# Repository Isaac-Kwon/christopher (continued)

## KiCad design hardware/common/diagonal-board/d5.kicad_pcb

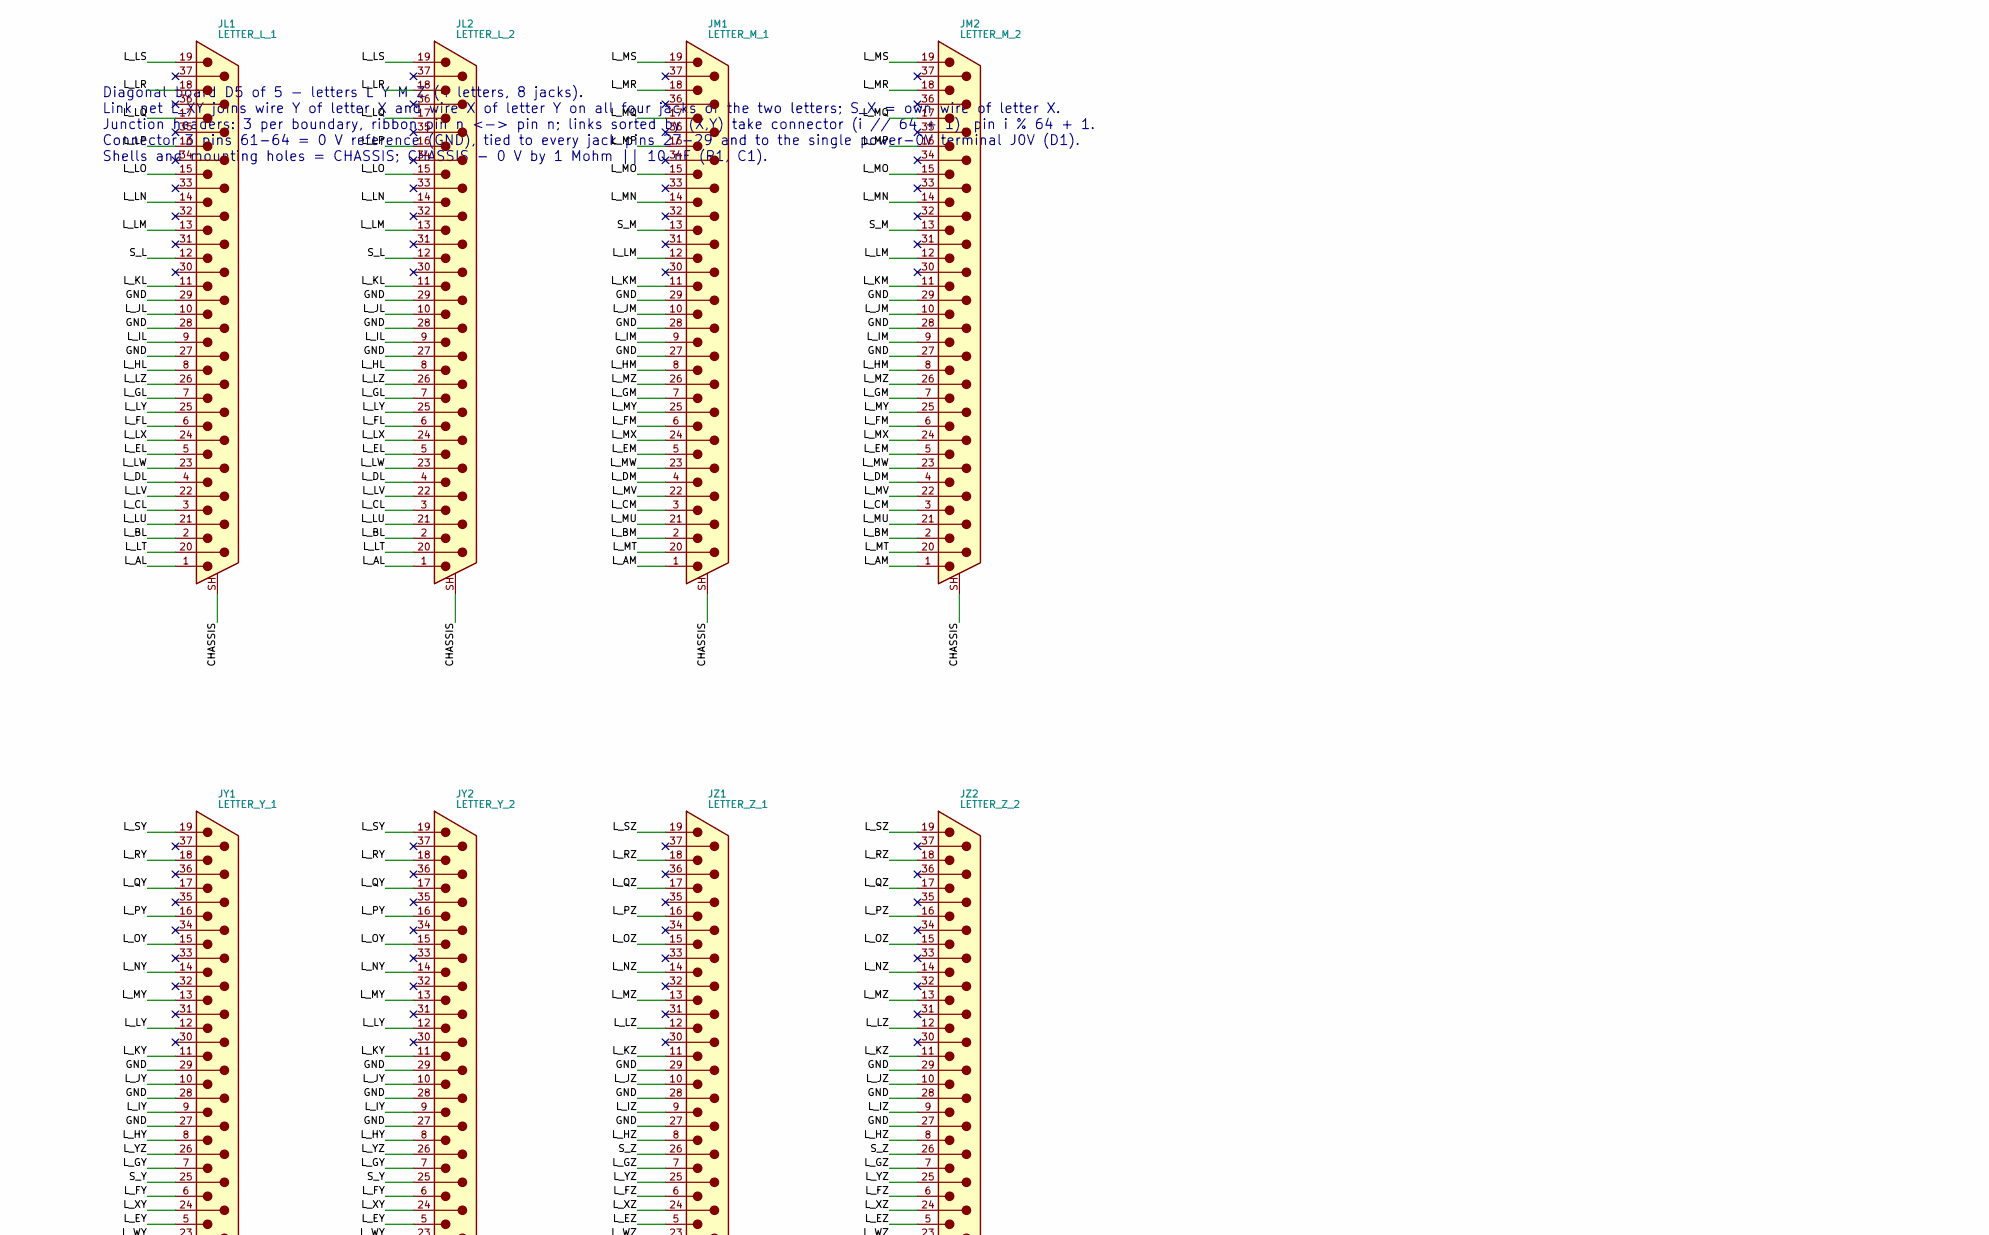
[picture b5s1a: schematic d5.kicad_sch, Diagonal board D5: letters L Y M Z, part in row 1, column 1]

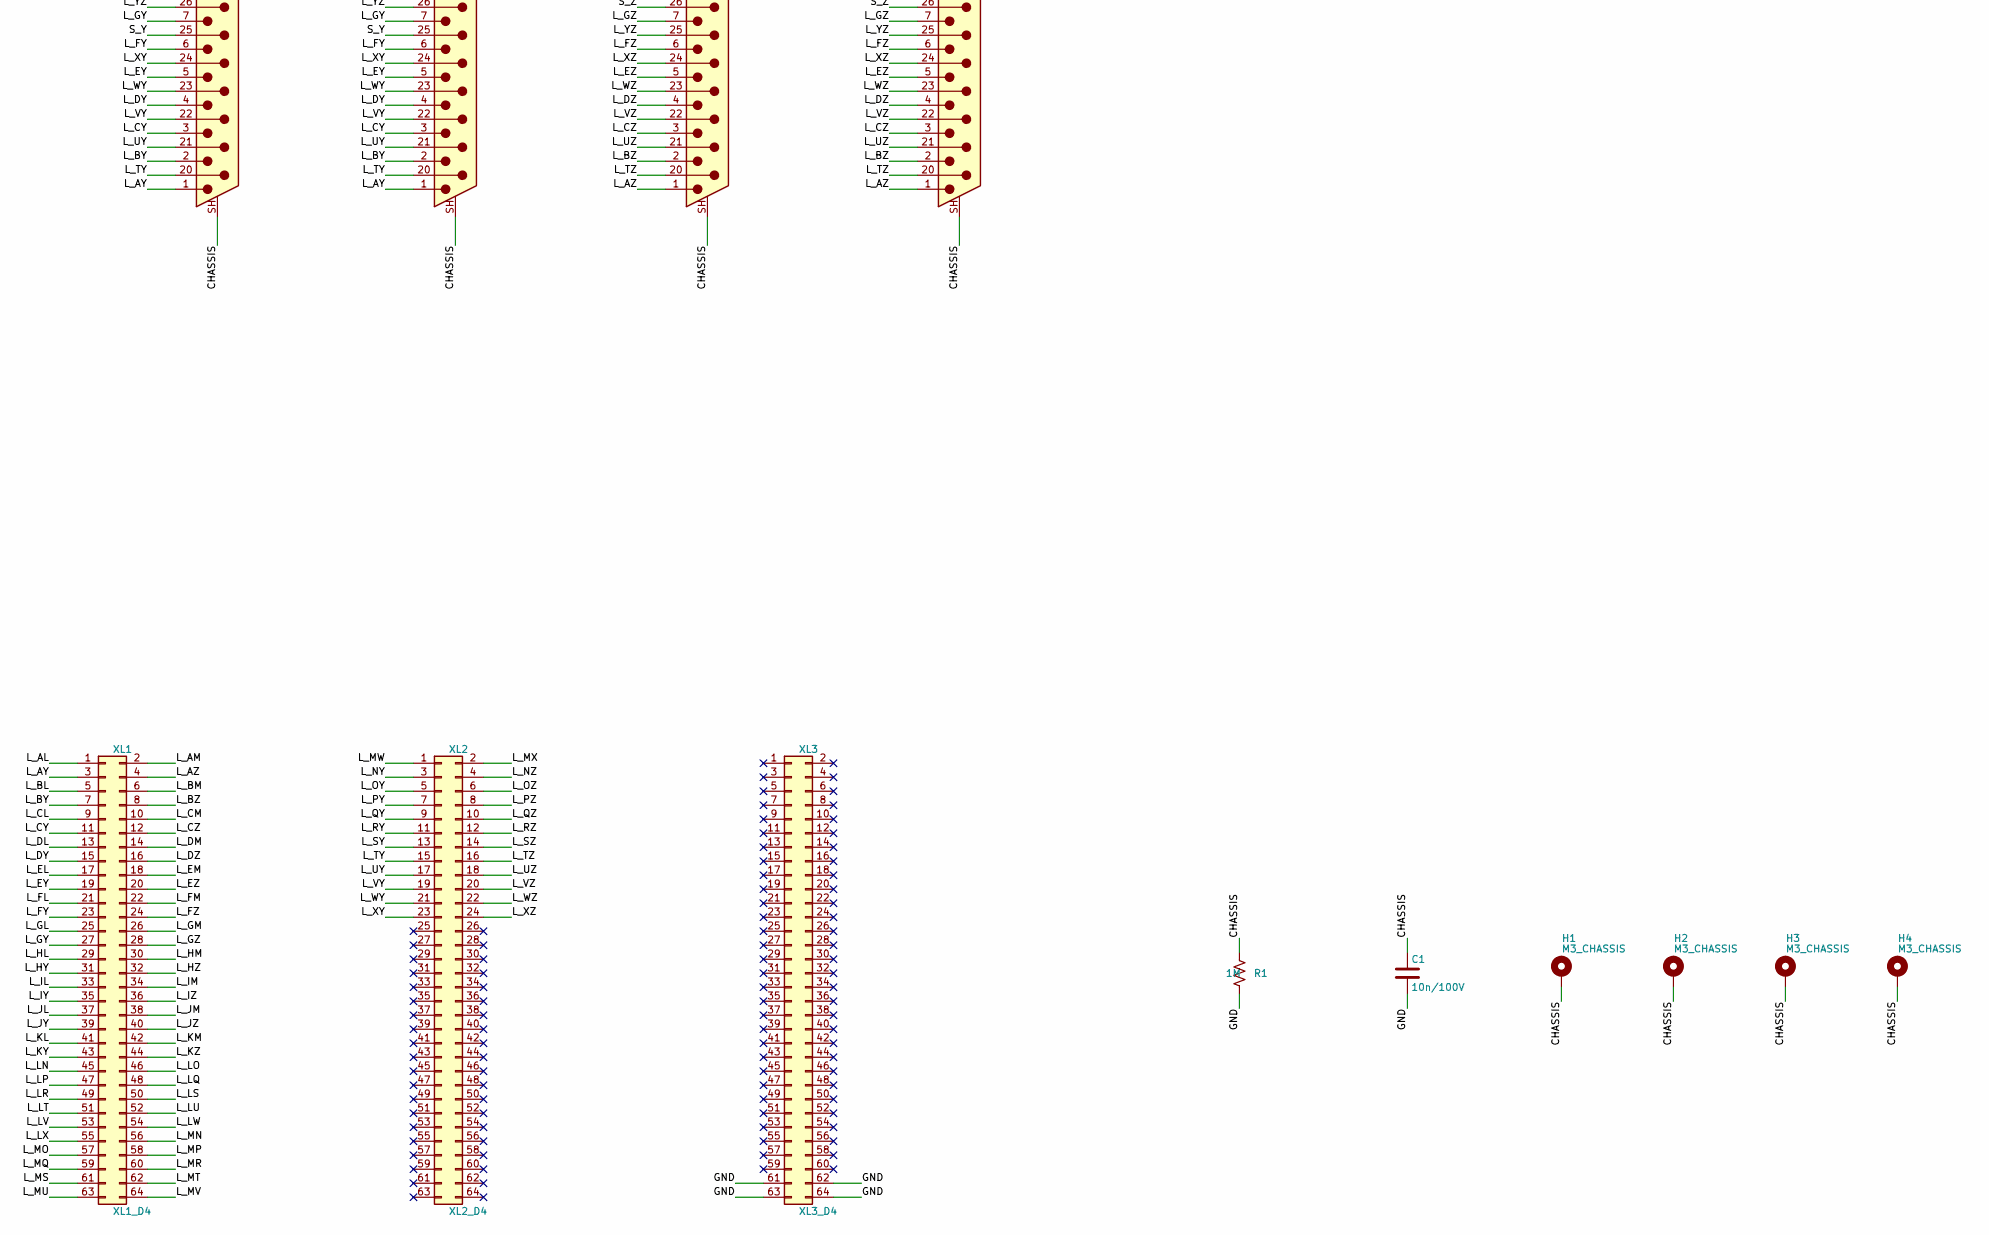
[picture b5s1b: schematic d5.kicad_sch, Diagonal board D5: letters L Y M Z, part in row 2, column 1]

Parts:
C1: 10n/100V; C_0805_2012Metric
H1, H2, H3, H4: M3_CHASSIS; MountingHole_3.2mm_M3_Pad
JL1: LETTER_L_1; DSUB-37_Pins_Vertical_P2.77x2.84mm_MountingHoles
JL2: LETTER_L_2; DSUB-37_Pins_Vertical_P2.77x2.84mm_MountingHoles
JM1: LETTER_M_1; DSUB-37_Pins_Vertical_P2.77x2.84mm_MountingHoles
JM2: LETTER_M_2; DSUB-37_Pins_Vertical_P2.77x2.84mm_MountingHoles
JY1: LETTER_Y_1; DSUB-37_Pins_Vertical_P2.77x2.84mm_MountingHoles
JY2: LETTER_Y_2; DSUB-37_Pins_Vertical_P2.77x2.84mm_MountingHoles
JZ1: LETTER_Z_1; DSUB-37_Pins_Vertical_P2.77x2.84mm_MountingHoles
JZ2: LETTER_Z_2; DSUB-37_Pins_Vertical_P2.77x2.84mm_MountingHoles
R1: 1M; R_0603_1608Metric
XL1: XL1_D4; IDC-Header_2x32_P2.54mm_Vertical
XL2: XL2_D4; IDC-Header_2x32_P2.54mm_Vertical
XL3: XL3_D4; IDC-Header_2x32_P2.54mm_Vertical

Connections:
/CHASSIS: C1.1, H1.1, H2.1, H3.1, H4.1, JL1.SH (PAD), JL2.SH (PAD), JM1.SH (PAD), JM2.SH (PAD), JY1.SH (PAD), JY2.SH (PAD), JZ1.SH (PAD), JZ2.SH (PAD), R1.1
/GND: C1.2, JL1.27, JL1.28, JL1.29, JL2.27, JL2.28, JL2.29, JM1.27, JM1.28, JM1.29, JM2.27, JM2.28, JM2.29, JY1.27, JY1.28, JY1.29, JY2.27, JY2.28, JY2.29, JZ1.27, JZ1.28, JZ1.29, JZ2.27, JZ2.28, JZ2.29, R1.2, XL3.61, XL3.62, XL3.63, XL3.64
/L_AL: JL1.1, JL2.1, XL1.1
/L_AM: JM1.1, JM2.1, XL1.2
/L_AY: JY1.1, JY2.1, XL1.3
/L_AZ: JZ1.1, JZ2.1, XL1.4
/L_BL: JL1.2, JL2.2, XL1.5
/L_BM: JM1.2, JM2.2, XL1.6
/L_BY: JY1.2, JY2.2, XL1.7
/L_BZ: JZ1.2, JZ2.2, XL1.8
/L_CL: JL1.3, JL2.3, XL1.9
/L_CM: JM1.3, JM2.3, XL1.10
/L_CY: JY1.3, JY2.3, XL1.11
/L_CZ: JZ1.3, JZ2.3, XL1.12
/L_DL: JL1.4, JL2.4, XL1.13
/L_DM: JM1.4, JM2.4, XL1.14
/L_DY: JY1.4, JY2.4, XL1.15
/L_DZ: JZ1.4, JZ2.4, XL1.16
/L_EL: JL1.5, JL2.5, XL1.17
/L_EM: JM1.5, JM2.5, XL1.18
/L_EY: JY1.5, JY2.5, XL1.19
/L_EZ: JZ1.5, JZ2.5, XL1.20
/L_FL: JL1.6, JL2.6, XL1.21
/L_FM: JM1.6, JM2.6, XL1.22
/L_FY: JY1.6, JY2.6, XL1.23
/L_FZ: JZ1.6, JZ2.6, XL1.24
/L_GL: JL1.7, JL2.7, XL1.25
/L_GM: JM1.7, JM2.7, XL1.26
/L_GY: JY1.7, JY2.7, XL1.27
/L_GZ: JZ1.7, JZ2.7, XL1.28
/L_HL: JL1.8, JL2.8, XL1.29
/L_HM: JM1.8, JM2.8, XL1.30
/L_HY: JY1.8, JY2.8, XL1.31
/L_HZ: JZ1.8, JZ2.8, XL1.32
/L_IL: JL1.9, JL2.9, XL1.33
/L_IM: JM1.9, JM2.9, XL1.34
/L_IY: JY1.9, JY2.9, XL1.35
/L_IZ: JZ1.9, JZ2.9, XL1.36
/L_JL: JL1.10, JL2.10, XL1.37
/L_JM: JM1.10, JM2.10, XL1.38
/L_JY: JY1.10, JY2.10, XL1.39
/L_JZ: JZ1.10, JZ2.10, XL1.40
/L_KL: JL1.11, JL2.11, XL1.41
/L_KM: JM1.11, JM2.11, XL1.42
/L_KY: JY1.11, JY2.11, XL1.43
/L_KZ: JZ1.11, JZ2.11, XL1.44
/L_LM: JL1.13, JL2.13, JM1.12, JM2.12
/L_LN: JL1.14, JL2.14, XL1.45
/L_LO: JL1.15, JL2.15, XL1.46
/L_LP: JL1.16, JL2.16, XL1.47
/L_LQ: JL1.17, JL2.17, XL1.48
/L_LR: JL1.18, JL2.18, XL1.49
/L_LS: JL1.19, JL2.19, XL1.50
/L_LT: JL1.20, JL2.20, XL1.51
/L_LU: JL1.21, JL2.21, XL1.52
/L_LV: JL1.22, JL2.22, XL1.53
/L_LW: JL1.23, JL2.23, XL1.54
/L_LX: JL1.24, JL2.24, XL1.55
/L_LY: JL1.25, JL2.25, JY1.12, JY2.12
/L_LZ: JL1.26, JL2.26, JZ1.12, JZ2.12
/L_MN: JM1.14, JM2.14, XL1.56
/L_MO: JM1.15, JM2.15, XL1.57
/L_MP: JM1.16, JM2.16, XL1.58
/L_MQ: JM1.17, JM2.17, XL1.59
/L_MR: JM1.18, JM2.18, XL1.60
/L_MS: JM1.19, JM2.19, XL1.61
/L_MT: JM1.20, JM2.20, XL1.62
/L_MU: JM1.21, JM2.21, XL1.63
/L_MV: JM1.22, JM2.22, XL1.64
/L_MW: JM1.23, JM2.23, XL2.1
/L_MX: JM1.24, JM2.24, XL2.2
/L_MY: JM1.25, JM2.25, JY1.13, JY2.13
/L_MZ: JM1.26, JM2.26, JZ1.13, JZ2.13
/L_NY: JY1.14, JY2.14, XL2.3
/L_NZ: JZ1.14, JZ2.14, XL2.4
/L_OY: JY1.15, JY2.15, XL2.5
/L_OZ: JZ1.15, JZ2.15, XL2.6
/L_PY: JY1.16, JY2.16, XL2.7
/L_PZ: JZ1.16, JZ2.16, XL2.8
/L_QY: JY1.17, JY2.17, XL2.9
/L_QZ: JZ1.17, JZ2.17, XL2.10
/L_RY: JY1.18, JY2.18, XL2.11
/L_RZ: JZ1.18, JZ2.18, XL2.12
/L_SY: JY1.19, JY2.19, XL2.13
/L_SZ: JZ1.19, JZ2.19, XL2.14
/L_TY: JY1.20, JY2.20, XL2.15
/L_TZ: JZ1.20, JZ2.20, XL2.16
/L_UY: JY1.21, JY2.21, XL2.17
/L_UZ: JZ1.21, JZ2.21, XL2.18
/L_VY: JY1.22, JY2.22, XL2.19
/L_VZ: JZ1.22, JZ2.22, XL2.20
/L_WY: JY1.23, JY2.23, XL2.21
/L_WZ: JZ1.23, JZ2.23, XL2.22
/L_XY: JY1.24, JY2.24, XL2.23
/L_XZ: JZ1.24, JZ2.24, XL2.24
/L_YZ: JY1.26, JY2.26, JZ1.25, JZ2.25
/S_L: JL1.12, JL2.12
/S_M: JM1.13, JM2.13
/S_Y: JY1.25, JY2.25
/S_Z: JZ1.26, JZ2.26

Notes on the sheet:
Diagonal board D5 of 5 - letters L Y M Z (4 letters, 8 jacks). Link net L_XY joins wire Y of letter X and wire X of letter Y on all four jacks of the two letters; S_X = own wire of letter X. Junction headers: 3 per boundary, ribbon pin n <-> pin n; links sorted by (X,Y) take connector (i // 64 + 1)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

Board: 4 copper layers, 17 parts (3 on the bottom side), 100 nets, no tracks yet.
